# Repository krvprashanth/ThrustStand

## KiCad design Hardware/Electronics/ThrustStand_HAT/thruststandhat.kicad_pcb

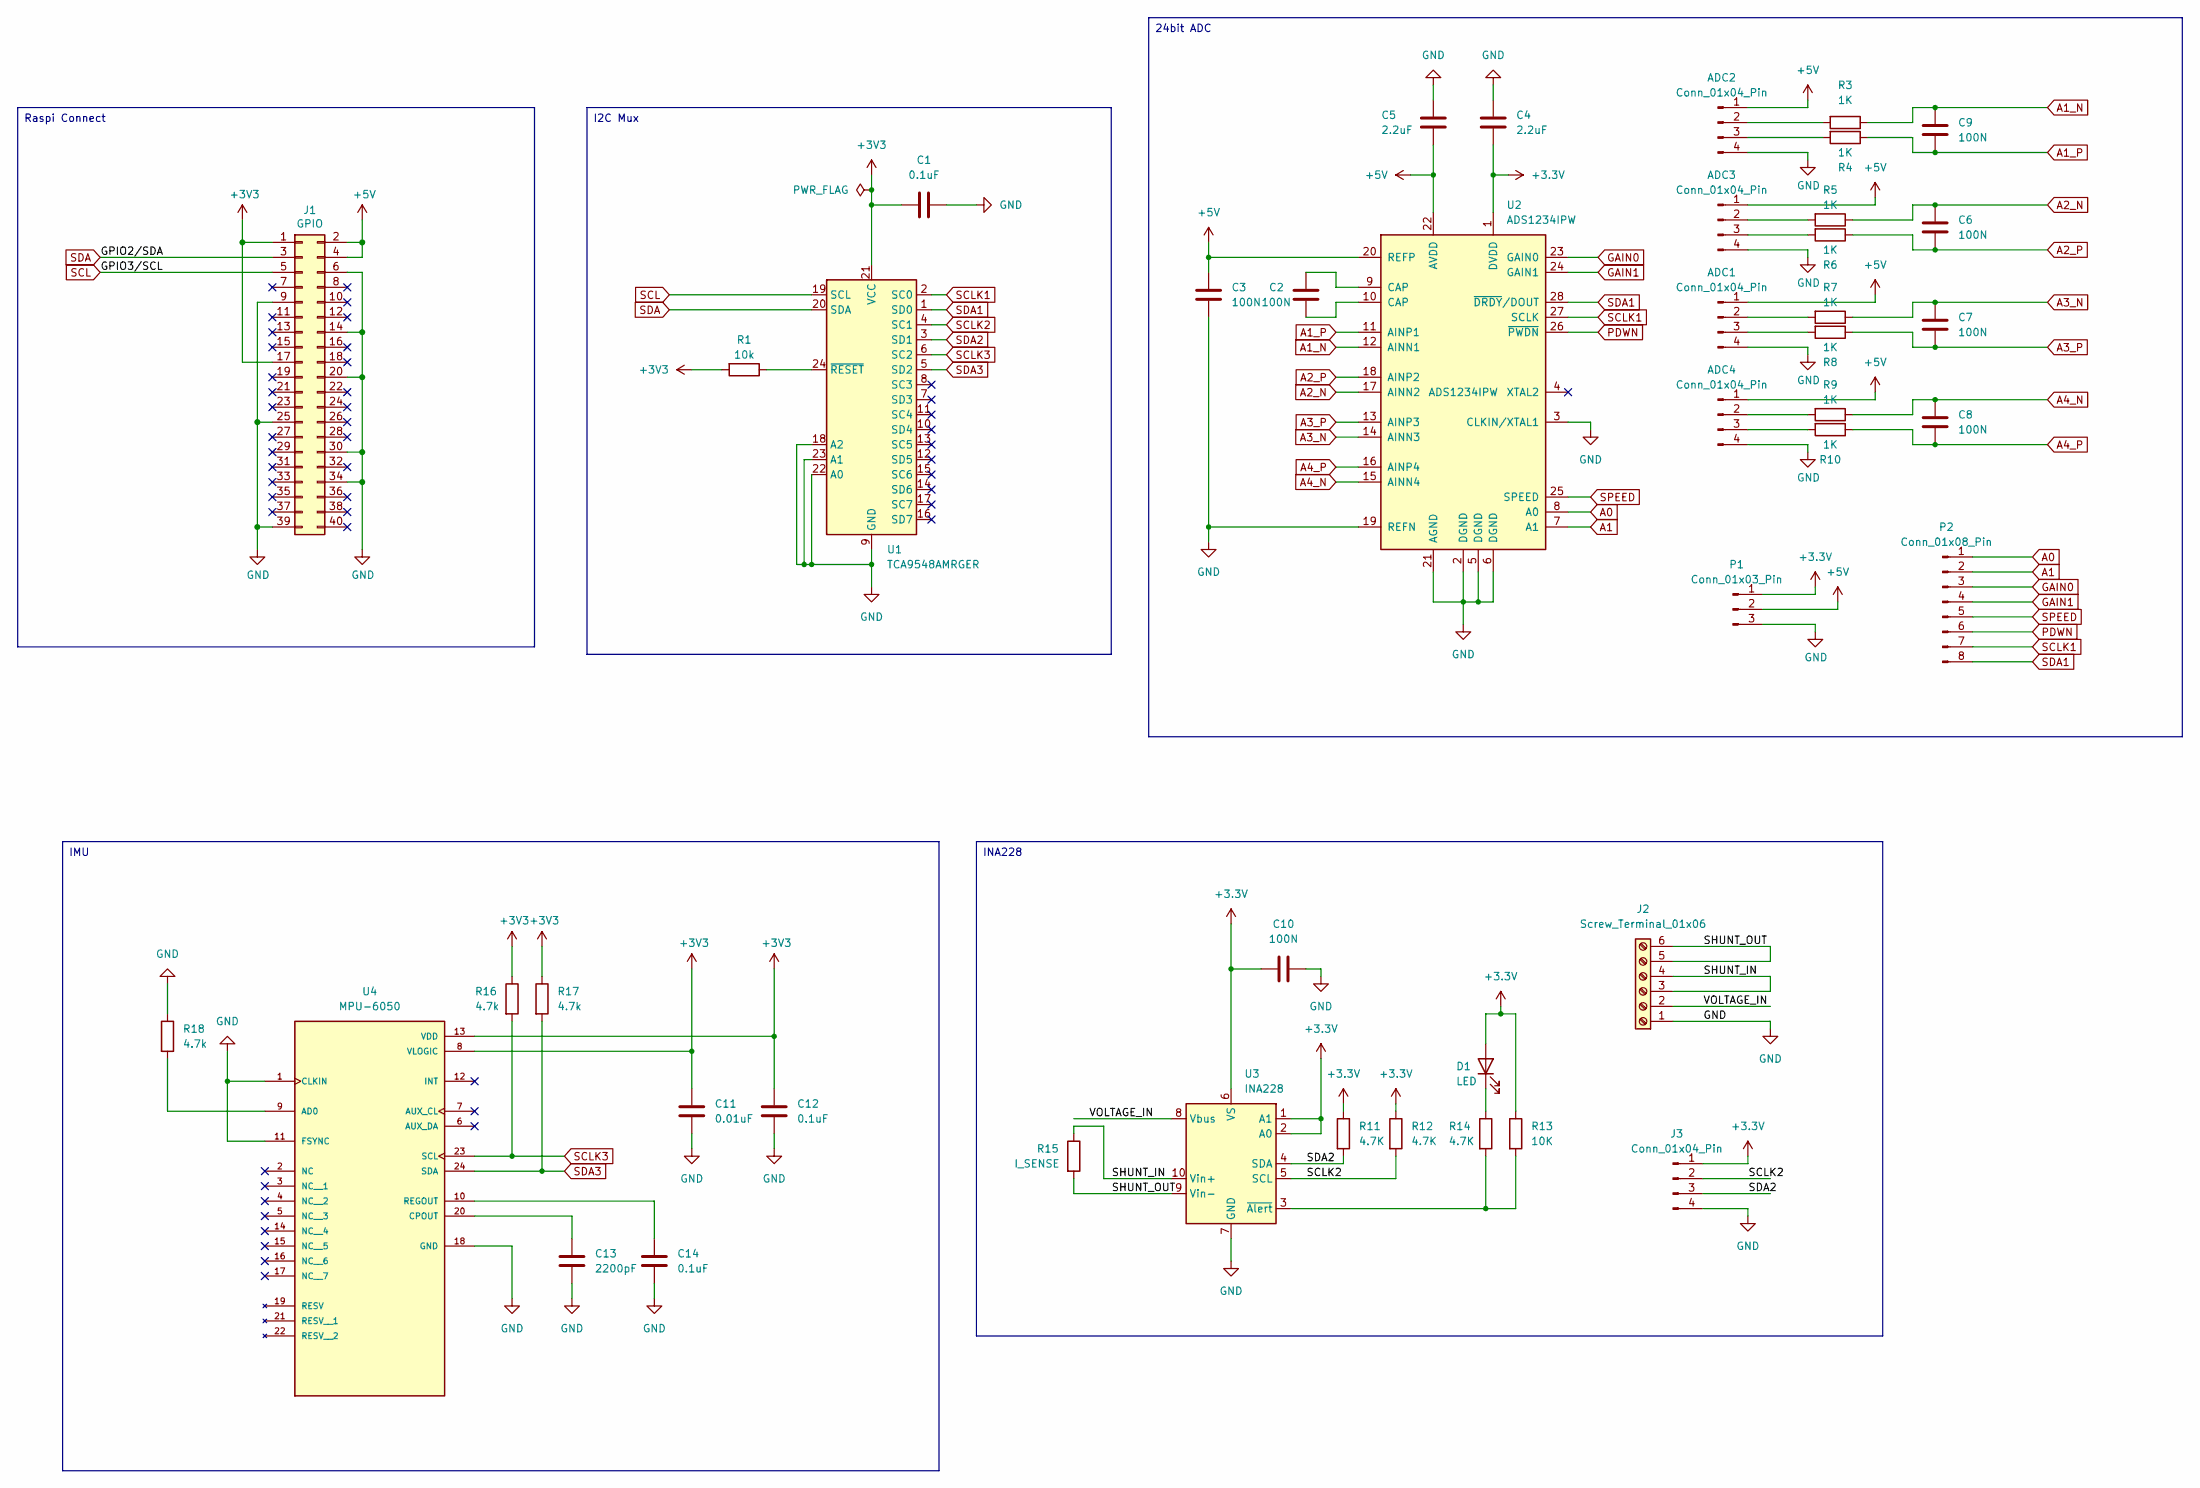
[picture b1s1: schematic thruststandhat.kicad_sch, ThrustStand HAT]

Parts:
ADC1, ADC2, ADC3, ADC4: Conn_01x04_Pin; PinHeader_1x04_P2.54mm_Vertical
C1, C12, C14: 0.1uF; C_0603_1608Metric
C2, C3, C6, C7, C8, C9, C10: 100N; C_0402_1005Metric
C4, C5: 2.2uF; C_0402_1005Metric
C11: 0.01uF; C_0603_1608Metric
C13: 2200pF; C_0402_1005Metric
D1: LED; LED_0603_1608Metric
J1: GPIO; PinSocket_2x20_P2.54mm_Vertical
J2: Screw_Terminal_01x06; TerminalBlock_4Ucon_1x06_P3.50mm_Vertical
J3: Conn_01x04_Pin; PinHeader_1x04_P2.54mm_Horizontal
P1: Conn_01x03_Pin; PinHeader_1x03_P2.54mm_Vertical
P2: Conn_01x08_Pin; PinHeader_1x08_P2.54mm_Vertical
R1: 10k; R_0603_1608Metric
R3, R4, R5, R6, R7, R8, R9, R10: 1K; R_0603_1608Metric
R11, R12, R14: 4.7K; R_0603_1608Metric
R13: 10K; R_0603_1608Metric
R15: I_SENSE; R_2512_6332Metric
R16, R17, R18: 4.7k; R_0603_1608Metric
U1: TCA9548AMRGER; Texas_RGE0024C_VQFN-24-1EP_4x4mm_P0.5mm_EP2.1x2.1mm; Manufacturer Part Numbe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 TCA9548AMRGER
U2: ADS1234IPW; TSSOP-28_4.4x7.8mm_P0.5mm; Manufacturer Part Numbe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 ADS1234IPW
U3: INA228; VSSOP-10_3x3mm_P0.5mm
U4: MPU-6050; QFN50P400X400X95-24N; PARTREV 3.4

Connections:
+3.3V: C4.2, C10.1, D1.2 (A), J3.1, P1.1, R11.1, R12.1, R13.1, U2.1 (DVDD), U3.1 (A1), U3.2 (A0), U3.6 (VS)
+3V3: C1.1, C11.1, C12.1, J1.1, J1.17, R1.2, R16.1, R17.1, U1.21 (VCC), U4.8 (VLOGIC), U4.13 (VDD)
+5V: ADC1.1, ADC2.1, ADC3.1, ADC4.1, C3.1, C5.2, J1.2, J1.4, P1.2, U2.20 (REFP), U2.22 (AVDD)
/GPIO4/GPCLK0: J1.7
/GPIO5: J1.29
/GPIO6: J1.31
/GPIO7/SPI0.CE1: J1.26
/GPIO8/SPI0.CE0: J1.24
/GPIO9/SPI0.MISO: J1.21
/GPIO10/SPI0.MOSI: J1.19
/GPIO11/SPI0.SCLK: J1.23
/GPIO12/PWM0: J1.32
/GPIO13/PWM1: J1.33
/GPIO14/TXD0: J1.8
/GPIO15/RXD0: J1.10
/GPIO16: J1.36
/GPIO17: J1.11
/GPIO18/PCM.CLK: J1.12
/GPIO19/PCM.FS: J1.35
/GPIO20/PCM.DIN: J1.38
/GPIO21/PCM.DOUT: J1.40
/GPIO22: J1.15
/GPIO23: J1.16
/GPIO24: J1.18
/GPIO25: J1.22
/GPIO26: J1.37
/GPIO27: J1.13
/ID_SCL: J1.28
/ID_SDA: J1.27
/SHUNT_IN: J2.3, J2.4, R15.1, U3.10 (Vin+)
/SHUNT_OUT: J2.5, J2.6, R15.2, U3.9 (Vin-)
/VOLTAGE_IN: J2.2, U3.8 (Vbus)
A0: P2.1, U2.8 (A0)
A1: P2.2, U2.7 (A1)
A1_N: C9.1, R3.1, U2.12 (AINN1)
A1_P: C9.2, R4.1, U2.11 (AINP1)
A2_N: C6.1, R5.1, U2.17 (AINN2)
A2_P: C6.2, R6.1, U2.18 (AINP2)
A3_N: C7.1, R7.1, U2.14 (AINN3)
A3_P: C7.2, R8.1, U2.13 (AINP3)
A4_N: C8.1, R9.1, U2.15 (AINN4)
A4_P: C8.2, R10.1, U2.16 (AINP4)
GAIN0: P2.3, U2.23 (GAIN0)
GAIN1: P2.4, U2.24 (GAIN1)
GND: ADC1.4, ADC2.4, ADC3.4, ADC4.4, C1.2, C3.2, C4.1, C5.1, C10.2, C11.2, C12.2, C13.2, C14.2, J1.6, J1.9, J1.14, J1.20, J1.25, J1.30, J1.34, J1.39, J2.1, J3.4, P1.3, R18.1, U1.9 (GND), U1.18 (A2), U1.22 (A0), U1.23 (A1), U2.2 (DGND), U2.3 (CLKIN/XTAL1), U2.5 (DGND), U2.6 (DGND), U2.19 (REFN), U2.21 (AGND), U3.7 (GND), U4.1 (CLKIN), U4.11 (FSYNC), U4.18 (GND)
unnamed: ADC1.2, R7.2
unnamed: ADC1.3, R8.2
unnamed: ADC2.2, R3.2
unnamed: ADC2.3, R4.2
unnamed: ADC3.2, R5.2
unnamed: ADC3.3, R6.2
unnamed: ADC4.2, R9.2
unnamed: ADC4.3, R10.2
unnamed: C2.1, U2.9 (CAP)
unnamed: C2.2, U2.10 (CAP)
unnamed: D1.1 (K), R14.1
unnamed: R1.1, U1.24 (~RESET)
unnamed: R13.2, R14.2, U3.3 (~Alert)
unnamed: R18.2, U4.9 (AD0)
unnamed: C13.1, U4.20 (CPOUT)
unnamed: C14.1, U4.10 (REGOUT)
PDWN: P2.6, U2.26 (~PWDN)
SCL: J1.5, U1.19 (SCL)
SCLK1: P2.7, U1.2 (SC0), U2.27 (SCLK)
SCLK2: J3.2, R12.2, U1.4 (SC1), U3.5 (SCL)
SCLK3: R16.2, U1.6 (SC2), U4.23 (SCL)
SDA: J1.3, U1.20 (SDA)
SDA1: P2.8, U1.1 (SD0), U2.28 (~DRDY/DOUT)
SDA2: J3.3, R11.2, U1.3 (SD1), U3.4 (SDA)
SDA3: R17.2, U1.5 (SD2), U4.24 (SDA)
SPEED: P2.5, U2.25 (SPEED)

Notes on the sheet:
IMU
I2C Mux
INA228
24bit ADC
Raspi Connect

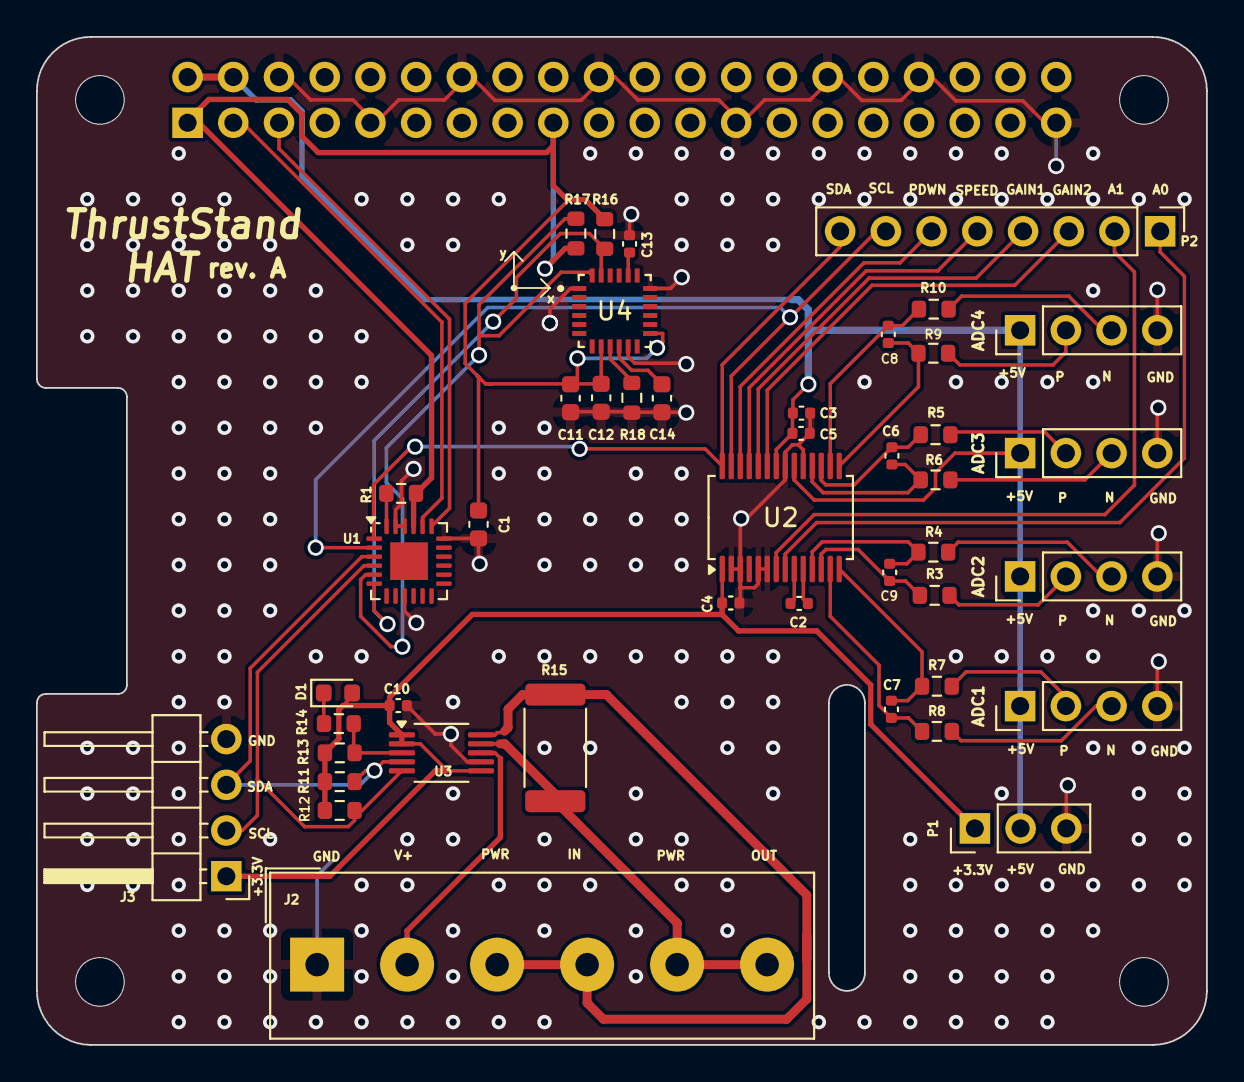
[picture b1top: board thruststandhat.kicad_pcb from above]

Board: 2 copper layers, 65.0 x 56.0 mm, 49 parts (1 on the bottom side), 45 nets.

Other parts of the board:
MH1, MH2, MH3, MH4: MountingHole_2.7mm_M2.5

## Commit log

2024-09-08 Add: ThrustStand HAT
